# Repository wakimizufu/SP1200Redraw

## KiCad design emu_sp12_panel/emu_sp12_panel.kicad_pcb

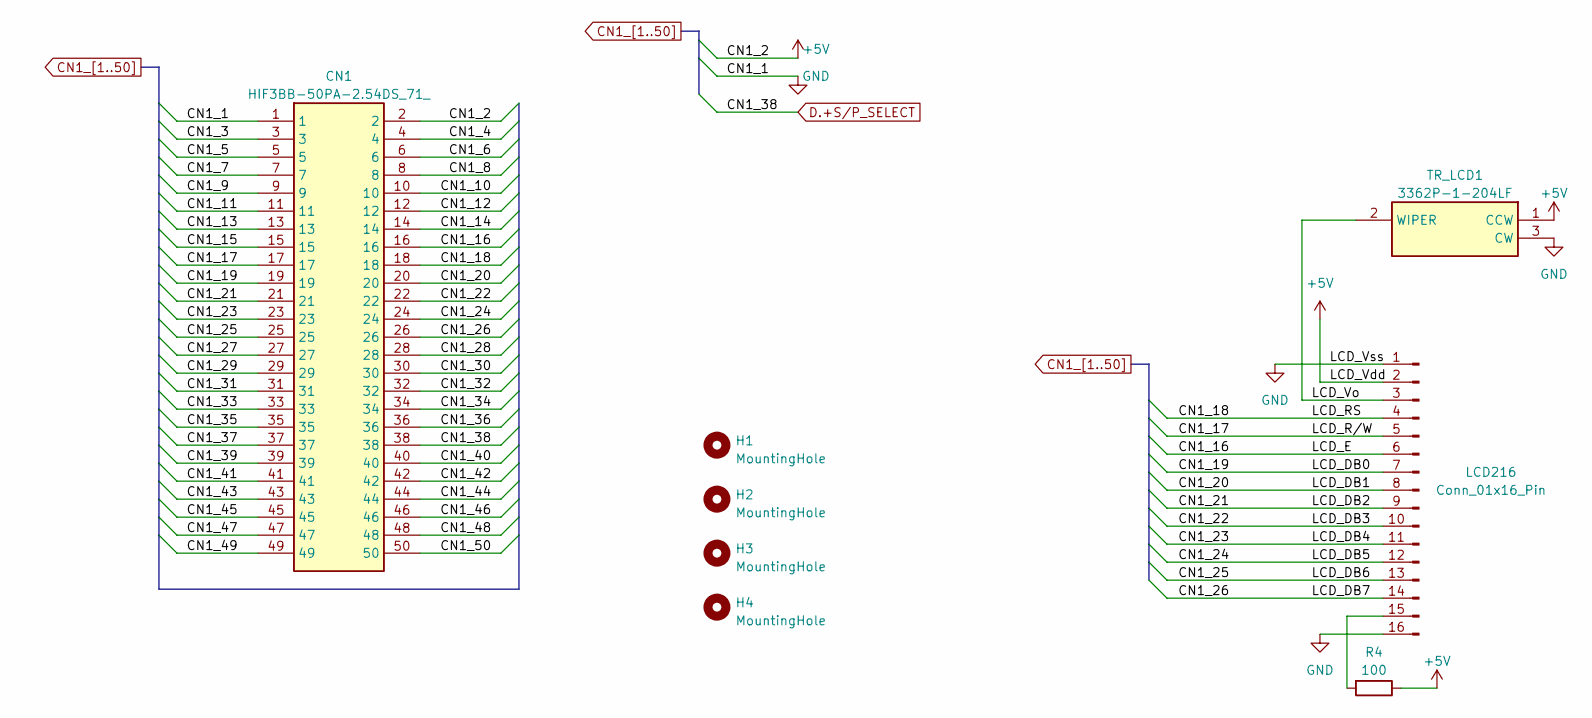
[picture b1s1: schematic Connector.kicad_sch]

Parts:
CN1: HIF3BB-50PA-2.54DS_71_; HIF3BB50PA254DS71; Manufacturer_Part_Number HIF3BB-50PA-2.54DS(71); Mouser Part Number 798-HIF3BB50PA254DS1
H1, H2, H3, H4: MountingHole; MountingHole_3.2mm_M3
LCD216: Conn_01x16_Pin; PinHeader_1x16_P2.54mm_Vertical
R4: 100; R_Axial_DIN0207_L6.3mm_D2.5mm_P5.08mm_Vertical
TR_LCD1: 3362P-1-204LF; 3362P_1; Manufacturer_Part_Number 3362P-1-103LF; Mouser Part Number 652-3362P-1-103LF

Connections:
/Connector/LCD_Vo: LCD216.3, TR_LCD1.2 (WIPER)
CN1_3: CN1.3; also elsewhere on the board
CN1_4: CN1.4; also elsewhere on the board
CN1_5: CN1.5; also elsewhere on the board
CN1_6: CN1.6; also elsewhere on the board
CN1_7: CN1.7; also elsewhere on the board
CN1_8: CN1.8; also elsewhere on the board
CN1_9: CN1.9; also elsewhere on the board
CN1_10: CN1.10
CN1_11: CN1.11; also elsewhere on the board
CN1_12: CN1.12; also elsewhere on the board
CN1_14: CN1.14; also elsewhere on the board
CN1_15: CN1.15; also elsewhere on the board
CN1_16: CN1.16, LCD216.6
CN1_17: CN1.17, LCD216.5
CN1_18: CN1.18, LCD216.4
CN1_19: CN1.19, LCD216.7
CN1_20: CN1.20, LCD216.8
CN1_21: CN1.21, LCD216.9
CN1_22: CN1.22, LCD216.10
CN1_23: CN1.23, LCD216.11
CN1_24: CN1.24, LCD216.12
CN1_25: CN1.25, LCD216.13
CN1_26: CN1.26, LCD216.14
CN1_27: CN1.27
CN1_28: CN1.28
CN1_29: CN1.29
CN1_30: CN1.30; also elsewhere on the board
CN1_31: CN1.31; also elsewhere on the board
CN1_32: CN1.32; also elsewhere on the board
CN1_33: CN1.33; also elsewhere on the board
CN1_34: CN1.34; also elsewhere on the board
CN1_35: CN1.35; also elsewhere on the board
CN1_36: CN1.36; also elsewhere on the board
CN1_37: CN1.37; also elsewhere on the board
CN1_39: CN1.39; also elsewhere on the board
CN1_40: CN1.40; also elsewhere on the board
CN1_41: CN1.41; also elsewhere on the board
CN1_42: CN1.42; also elsewhere on the board
CN1_43: CN1.43; also elsewhere on the board
CN1_44: CN1.44; also elsewhere on the board
CN1_45: CN1.45; also elsewhere on the board
CN1_46: CN1.46; also elsewhere on the board
CN1_47: CN1.47; also elsewhere on the board
CN1_48: CN1.48; also elsewhere on the board
CN1_49: CN1.49; also elsewhere on the board
CN1_50: CN1.50; also elsewhere on the board
D.+S/P_SELECT: CN1.38; also elsewhere on the board
GND: CN1.1, LCD216.1, LCD216.16, TR_LCD1.3 (CW); also elsewhere on the board

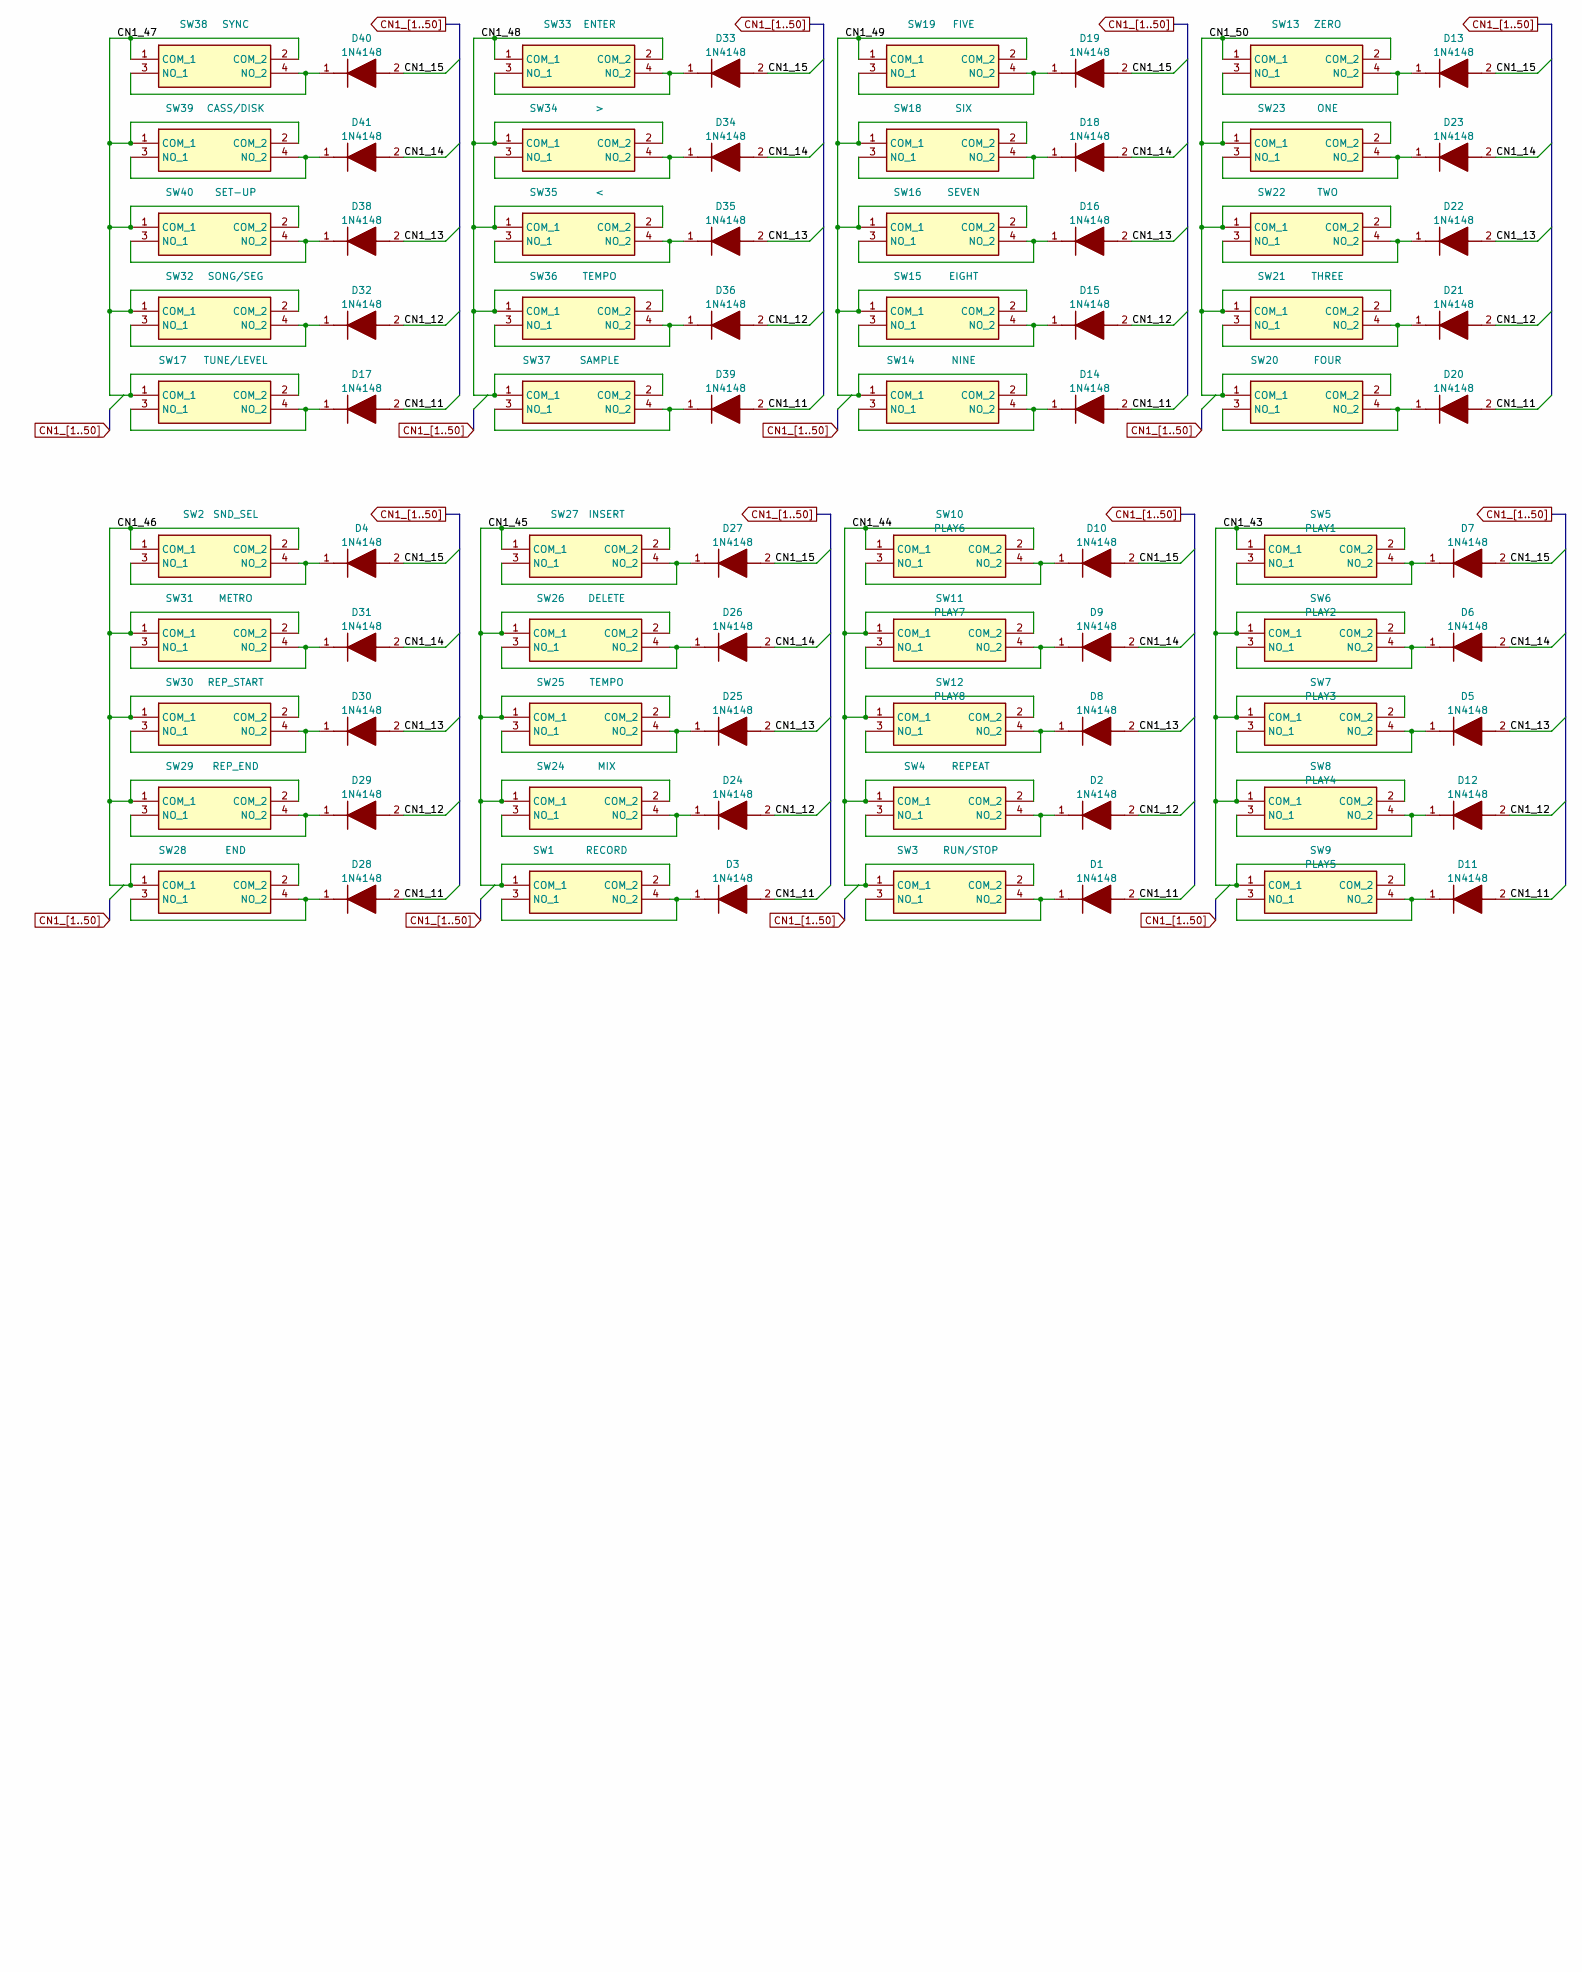
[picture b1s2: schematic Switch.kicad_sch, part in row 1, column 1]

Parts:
D1, D2, D3, D4, D5, D6, D7, D8, D9, D10, D11, D12, D13, D14, D15, D16, D17, D18, D19, D20, D21, D22, D23, D24, D25, D26, D27, D28, D29, D30, D31, D32, D33, D34, D35, D36, D38, D39, D40, D41: 1N4148; DIOAD1068W53L380D172; Manufacturer_Part_Number 1N4148; Mouser Part Number 512-1N4148
SW1: RECORD; DTS63NV; Manufacturer_Part_Number DTS-63N-V; Mouser Part Number 113-DTS-63N-V
SW2: SND_SEL; DTS63NV; Manufacturer_Part_Number DTS-63N-V; Mouser Part Number 113-DTS-63N-V
SW3: RUN/STOP; DTS63NV; Manufacturer_Part_Number DTS-63N-V; Mouser Part Number 113-DTS-63N-V
SW4: REPEAT; DTS63NV; Manufacturer_Part_Number DTS-63N-V; Mouser Part Number 113-DTS-63N-V
SW5: PLAY1; DTS63NV; Manufacturer_Part_Number TVGP01-G73BB
SW6: PLAY2; DTS63NV; Manufacturer_Part_Number TVGP01-G73BB
SW7: PLAY3; DTS63NV; Manufacturer_Part_Number TVGP01-G73BB
SW8: PLAY4; DTS63NV; Manufacturer_Part_Number TVGP01-G73BB
SW9: PLAY5; DTS63NV; Manufacturer_Part_Number TVGP01-G73BB
SW10: PLAY6; DTS63NV; Manufacturer_Part_Number TVGP01-G73BB
SW11: PLAY7; DTS63NV; Manufacturer_Part_Number TVGP01-G73BB
SW12: PLAY8; DTS63NV; Manufacturer_Part_Number TVGP01-G73BB
SW13: ZERO; DTS63NV; Manufacturer_Part_Number DTS-63N-V; Mouser Part Number 113-DTS-63N-V
SW14: NINE; DTS63NV; Manufacturer_Part_Number DTS-63N-V; Mouser Part Number 113-DTS-63N-V
SW15: EIGHT; DTS63NV; Manufacturer_Part_Number DTS-63N-V; Mouser Part Number 113-DTS-63N-V
SW16: SEVEN; DTS63NV; Manufacturer_Part_Number DTS-63N-V; Mouser Part Number 113-DTS-63N-V
SW17: TUNE/LEVEL; DTS63NV; Manufacturer_Part_Number DTS-63N-V; Mouser Part Number 113-DTS-63N-V
SW18: SIX; DTS63NV; Manufacturer_Part_Number DTS-63N-V; Mouser Part Number 113-DTS-63N-V
SW19: FIVE; DTS63NV; Manufacturer_Part_Number DTS-63N-V; Mouser Part Number 113-DTS-63N-V
SW20: FOUR; DTS63NV; Manufacturer_Part_Number DTS-63N-V; Mouser Part Number 113-DTS-63N-V
SW21: THREE; DTS63NV; Manufacturer_Part_Number DTS-63N-V; Mouser Part Number 113-DTS-63N-V
SW22: TWO; DTS63NV; Manufacturer_Part_Number DTS-63N-V; Mouser Part Number 113-DTS-63N-V
SW23: ONE; DTS63NV; Manufacturer_Part_Number DTS-63N-V; Mouser Part Number 113-DTS-63N-V
SW24: MIX; DTS63NV; Manufacturer_Part_Number DTS-63N-V; Mouser Part Number 113-DTS-63N-V
SW25, SW36: TEMPO; DTS63NV; Manufacturer_Part_Number DTS-63N-V; Mouser Part Number 113-DTS-63N-V
SW26: DELETE; DTS63NV; Manufacturer_Part_Number DTS-63N-V; Mouser Part Number 113-DTS-63N-V
SW27: INSERT; DTS63NV; Manufacturer_Part_Number DTS-63N-V; Mouser Part Number 113-DTS-63N-V
SW28: END; DTS63NV; Manufacturer_Part_Number DTS-63N-V; Mouser Part Number 113-DTS-63N-V
SW29: REP_END; DTS63NV; Manufacturer_Part_Number DTS-63N-V; Mouser Part Number 113-DTS-63N-V
SW30: REP_START; DTS63NV; Manufacturer_Part_Number DTS-63N-V; Mouser Part Number 113-DTS-63N-V
SW31: METRO; DTS63NV; Manufacturer_Part_Number DTS-63N-V; Mouser Part Number 113-DTS-63N-V
SW32: SONG/SEG; DTS63NV; Manufacturer_Part_Number DTS-63N-V; Mouser Part Number 113-DTS-63N-V
SW33: ENTER; DTS63NV; Manufacturer_Part_Number DTS-63N-V; Mouser Part Number 113-DTS-63N-V
SW34: >; DTS63NV; Manufacturer_Part_Number DTS-63N-V; Mouser Part Number 113-DTS-63N-V
SW35: <; DTS63NV; Manufacturer_Part_Number DTS-63N-V; Mouser Part Number 113-DTS-63N-V
SW37: SAMPLE; DTS63NV; Manufacturer_Part_Number DTS-63N-V; Mouser Part Number 113-DTS-63N-V
SW38: SYNC; DTS63NV; Manufacturer_Part_Number DTS-63N-V; Mouser Part Number 113-DTS-63N-V
SW39: CASS/DISK; DTS63NV; Manufacturer_Part_Number DTS-63N-V; Mouser Part Number 113-DTS-63N-V
SW40: SET-UP; DTS63NV; Manufacturer_Part_Number DTS-63N-V; Mouser Part Number 113-DTS-63N-V

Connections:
CN1_11: D1.2 (A), D3.2 (A), D11.2 (A), D14.2 (A), D17.2 (A), D20.2 (A), D28.2 (A), D39.2 (A); also elsewhere on the board
CN1_12: D2.2 (A), D12.2 (A), D15.2 (A), D21.2 (A), D24.2 (A), D29.2 (A), D32.2 (A), D36.2 (A); also elsewhere on the board
CN1_14: D6.2 (A), D9.2 (A), D18.2 (A), D23.2 (A), D26.2 (A), D31.2 (A), D34.2 (A), D41.2 (A); also elsewhere on the board
CN1_15: D4.2 (A), D7.2 (A), D10.2 (A), D13.2 (A), D19.2 (A), D27.2 (A), D33.2 (A), D40.2 (A); also elsewhere on the board
CN1_43: SW5.1 (COM_1), SW5.2 (COM_2), SW6.1 (COM_1), SW6.2 (COM_2), SW7.1 (COM_1), SW7.2 (COM_2), SW8.1 (COM_1), SW8.2 (COM_2), SW9.1 (COM_1), SW9.2 (COM_2); also elsewhere on the board
CN1_44: SW3.1 (COM_1), SW3.2 (COM_2), SW4.1 (COM_1), SW4.2 (COM_2), SW10.1 (COM_1), SW10.2 (COM_2), SW11.1 (COM_1), SW11.2 (COM_2), SW12.1 (COM_1), SW12.2 (COM_2); also elsewhere on the board
CN1_45: SW1.1 (COM_1), SW1.2 (COM_2), SW24.1 (COM_1), SW24.2 (COM_2), SW25.1 (COM_1), SW25.2 (COM_2), SW26.1 (COM_1), SW26.2 (COM_2), SW27.1 (COM_1), SW27.2 (COM_2); also elsewhere on the board
CN1_46: SW2.1 (COM_1), SW2.2 (COM_2), SW28.1 (COM_1), SW28.2 (COM_2), SW29.1 (COM_1), SW29.2 (COM_2), SW30.1 (COM_1), SW30.2 (COM_2), SW31.1 (COM_1), SW31.2 (COM_2); also elsewhere on the board
CN1_47: SW17.1 (COM_1), SW17.2 (COM_2), SW32.1 (COM_1), SW32.2 (COM_2), SW38.1 (COM_1), SW38.2 (COM_2), SW39.1 (COM_1), SW39.2 (COM_2), SW40.1 (COM_1), SW40.2 (COM_2); also elsewhere on the board
CN1_48: SW33.1 (COM_1), SW33.2 (COM_2), SW34.1 (COM_1), SW34.2 (COM_2), SW35.1 (COM_1), SW35.2 (COM_2), SW36.1 (COM_1), SW36.2 (COM_2), SW37.1 (COM_1), SW37.2 (COM_2); also elsewhere on the board
CN1_49: SW14.1 (COM_1), SW14.2 (COM_2), SW15.1 (COM_1), SW15.2 (COM_2), SW16.1 (COM_1), SW16.2 (COM_2), SW18.1 (COM_1), SW18.2 (COM_2), SW19.1 (COM_1), SW19.2 (COM_2); also elsewhere on the board
CN1_50: SW13.1 (COM_1), SW13.2 (COM_2), SW20.1 (COM_1), SW20.2 (COM_2), SW21.1 (COM_1), SW21.2 (COM_2), SW22.1 (COM_1), SW22.2 (COM_2), SW23.1 (COM_1), SW23.2 (COM_2); also elsewhere on the board
unnamed: D1.1 (K), SW3.3 (NO_1), SW3.4 (NO_2)
unnamed: D2.1 (K), SW4.3 (NO_1), SW4.4 (NO_2)
unnamed: D3.1 (K), SW1.3 (NO_1), SW1.4 (NO_2)
unnamed: D4.1 (K), SW2.3 (NO_1), SW2.4 (NO_2)
unnamed: D5.1 (K), SW7.3 (NO_1), SW7.4 (NO_2)
unnamed: D6.1 (K), SW6.3 (NO_1), SW6.4 (NO_2)
unnamed: D7.1 (K), SW5.3 (NO_1), SW5.4 (NO_2)
unnamed: D8.1 (K), SW12.3 (NO_1), SW12.4 (NO_2)
unnamed: D9.1 (K), SW11.3 (NO_1), SW11.4 (NO_2)
unnamed: D10.1 (K), SW10.3 (NO_1), SW10.4 (NO_2)
unnamed: D11.1 (K), SW9.3 (NO_1), SW9.4 (NO_2)
unnamed: D12.1 (K), SW8.3 (NO_1), SW8.4 (NO_2)
unnamed: D13.1 (K), SW13.3 (NO_1), SW13.4 (NO_2)
unnamed: D14.1 (K), SW14.3 (NO_1), SW14.4 (NO_2)
unnamed: D15.1 (K), SW15.3 (NO_1), SW15.4 (NO_2)
unnamed: D16.1 (K), SW16.3 (NO_1), SW16.4 (NO_2)
unnamed: D17.1 (K), SW17.3 (NO_1), SW17.4 (NO_2)
unnamed: D18.1 (K), SW18.3 (NO_1), SW18.4 (NO_2)
unnamed: D19.1 (K), SW19.3 (NO_1), SW19.4 (NO_2)
unnamed: D20.1 (K), SW20.3 (NO_1), SW20.4 (NO_2)
unnamed: D21.1 (K), SW21.3 (NO_1), SW21.4 (NO_2)
unnamed: D22.1 (K), SW22.3 (NO_1), SW22.4 (NO_2)
unnamed: D23.1 (K), SW23.3 (NO_1), SW23.4 (NO_2)
unnamed: D24.1 (K), SW24.3 (NO_1), SW24.4 (NO_2)
unnamed: D25.1 (K), SW25.3 (NO_1), SW25.4 (NO_2)
unnamed: D26.1 (K), SW26.3 (NO_1), SW26.4 (NO_2)
unnamed: D27.1 (K), SW27.3 (NO_1), SW27.4 (NO_2)
unnamed: D28.1 (K), SW28.3 (NO_1), SW28.4 (NO_2)
unnamed: D29.1 (K), SW29.3 (NO_1), SW29.4 (NO_2)
unnamed: D30.1 (K), SW30.3 (NO_1), SW30.4 (NO_2)
unnamed: D31.1 (K), SW31.3 (NO_1), SW31.4 (NO_2)
unnamed: D32.1 (K), SW32.3 (NO_1), SW32.4 (NO_2)
unnamed: D33.1 (K), SW33.3 (NO_1), SW33.4 (NO_2)
unnamed: D34.1 (K), SW34.3 (NO_1), SW34.4 (NO_2)
unnamed: D35.1 (K), SW35.3 (NO_1), SW35.4 (NO_2)
unnamed: D36.1 (K), SW36.3 (NO_1), SW36.4 (NO_2)
unnamed: D39.1 (K), SW37.3 (NO_1), SW37.4 (NO_2)
unnamed: D40.1 (K), SW38.3 (NO_1), SW38.4 (NO_2)
unnamed: D41.1 (K), SW39.3 (NO_1), SW39.4 (NO_2)

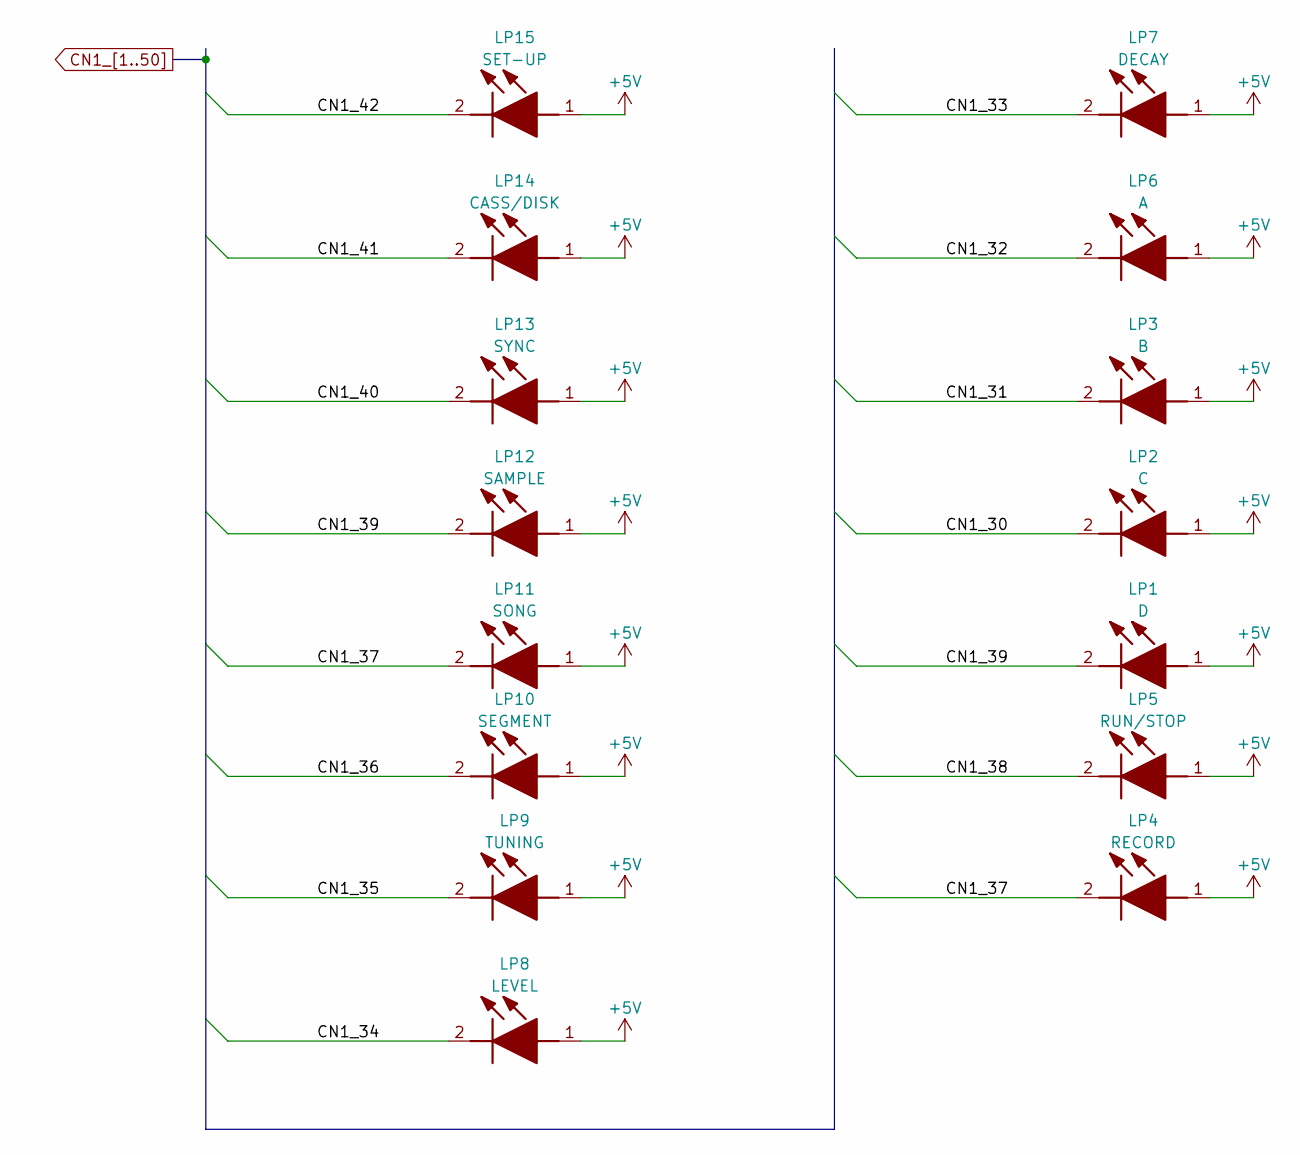
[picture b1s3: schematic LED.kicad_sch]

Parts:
LP1: D; LTL1CHKGKNN; Manufacturer_Part_Number LTL1CHKGKNN; Mouser Part Number 859-LTL1CHKGKNN
LP2: C; LTL1CHKGKNN; Manufacturer_Part_Number LTL1CHKGKNN; Mouser Part Number 859-LTL1CHKGKNN
LP3: B; LTL1CHKGKNN; Manufacturer_Part_Number LTL1CHKGKNN; Mouser Part Number 859-LTL1CHKGKNN
LP4: RECORD; LTL1CHKGKNN; Manufacturer_Part_Number LTL1CHKGKNN; Mouser Part Number 859-LTL1CHKGKNN
LP5: RUN/STOP; LTL1CHKGKNN; Manufacturer_Part_Number LTL1CHKGKNN; Mouser Part Number 859-LTL1CHKGKNN
LP6: A; LTL1CHKGKNN; Manufacturer_Part_Number LTL1CHKGKNN; Mouser Part Number 859-LTL1CHKGKNN
LP7: DECAY; LTL1CHKGKNN; Manufacturer_Part_Number LTL1CHKGKNN; Mouser Part Number 859-LTL1CHKGKNN
LP8: LEVEL; LTL1CHKGKNN; Manufacturer_Part_Number LTL1CHKGKNN; Mouser Part Number 859-LTL1CHKGKNN
LP9: TUNING; LTL1CHKGKNN; Manufacturer_Part_Number LTL1CHKGKNN; Mouser Part Number 859-LTL1CHKGKNN
LP10: SEGMENT; LTL1CHKGKNN; Manufacturer_Part_Number LTL1CHKGKNN; Mouser Part Number 859-LTL1CHKGKNN
LP11: SONG; LTL1CHKGKNN; Manufacturer_Part_Number LTL1CHKGKNN; Mouser Part Number 859-LTL1CHKGKNN
LP12: SAMPLE; LTL1CHKGKNN; Manufacturer_Part_Number LTL1CHKGKNN; Mouser Part Number 859-LTL1CHKGKNN
LP13: SYNC; LTL1CHKGKNN; Manufacturer_Part_Number LTL1CHKGKNN; Mouser Part Number 859-LTL1CHKGKNN
LP14: CASS/DISK; LTL1CHKGKNN; Manufacturer_Part_Number LTL1CHKGKNN; Mouser Part Number 859-LTL1CHKGKNN
LP15: SET-UP; LTL1CHKGKNN; Manufacturer_Part_Number LTL1CHKGKNN; Mouser Part Number 859-LTL1CHKGKNN

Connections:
CN1_30: LP2.2 (K); also elsewhere on the board
CN1_31: LP3.2 (K); also elsewhere on the board
CN1_32: LP6.2 (K); also elsewhere on the board
CN1_33: LP7.2 (K); also elsewhere on the board
CN1_34: LP8.2 (K); also elsewhere on the board
CN1_35: LP9.2 (K); also elsewhere on the board
CN1_36: LP10.2 (K); also elsewhere on the board
CN1_37: LP4.2 (K), LP11.2 (K); also elsewhere on the board
CN1_38: LP5.2 (K)
CN1_39: LP1.2 (K), LP12.2 (K); also elsewhere on the board
CN1_40: LP13.2 (K); also elsewhere on the board
CN1_41: LP14.2 (K); also elsewhere on the board
CN1_42: LP15.2 (K); also elsewhere on the board

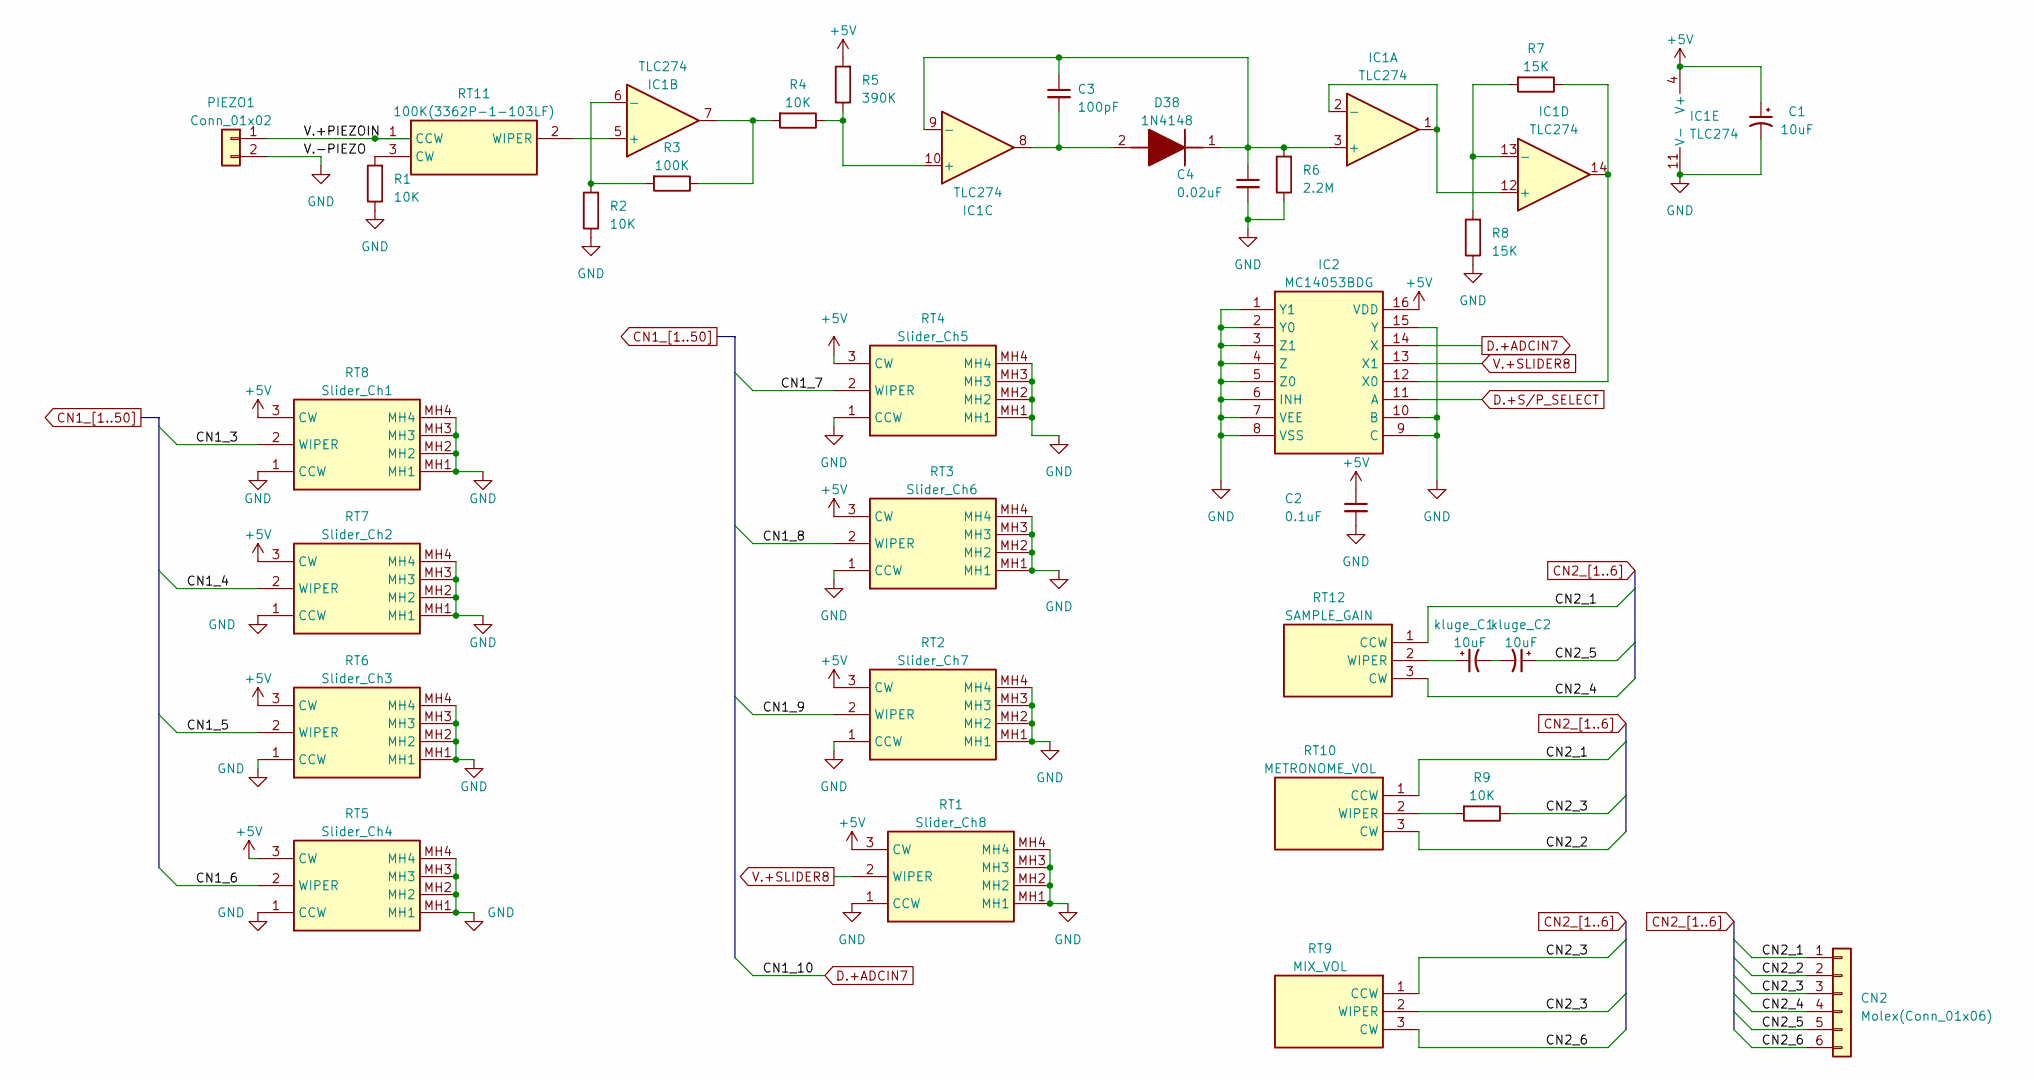
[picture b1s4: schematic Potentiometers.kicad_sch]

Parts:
C1: 10uF; CP_Radial_D5.0mm_P2.50mm
C2: 0.1uF; C_Rect_L7.0mm_W2.0mm_P5.00mm
C3: 100pF; C_Disc_D3.0mm_W2.0mm_P2.50mm
C4: 0.02uF; C_Rect_L7.0mm_W3.5mm_P5.00mm
CN2: Molex(Conn_01x06); PinHeader_1x06_P2.54mm_Vertical
D38: 1N4148; DIOAD1068W53L380D172; Manufacturer_Part_Number 1N4148; Mouser Part Number 512-1N4148
IC1: TLC274; DIP-14_W7.62mm_LongPads
IC2: MC14053BDG; DIP-16_W7.62mm_LongPads; Manufacturer_Part_Number MC14053BDG; Mouser Part Number 863-MC14053BDG
PIEZO1: Conn_01x02; PinHeader_1x02_P2.54mm_Vertical
R1, R2, R4, R9: 10K; R_Axial_DIN0207_L6.3mm_D2.5mm_P5.08mm_Vertical
R3: 100K; R_Axial_DIN0207_L6.3mm_D2.5mm_P5.08mm_Vertical
R5: 390K; R_Axial_DIN0207_L6.3mm_D2.5mm_P5.08mm_Vertical
R6: 2.2M; R_Axial_DIN0207_L6.3mm_D2.5mm_P5.08mm_Vertical
R7, R8: 15K; R_Axial_DIN0207_L6.3mm_D2.5mm_P5.08mm_Vertical
RT1: Slider_Ch8; PTA20432015DPB103; Manufacturer_Part_Number PTA2043-2015DPB103; Mouser Part Number 652-PTA2432015DPB103
RT2: Slider_Ch7; PTA20432015DPB103; Manufacturer_Part_Number PTA2043-2015DPB103; Mouser Part Number 652-PTA2432015DPB103
RT3: Slider_Ch6; PTA20432015DPB103; Manufacturer_Part_Number PTA2043-2015DPB103; Mouser Part Number 652-PTA2432015DPB103
RT4: Slider_Ch5; PTA20432015DPB103; Manufacturer_Part_Number PTA2043-2015DPB103; Mouser Part Number 652-PTA2432015DPB103
RT5: Slider_Ch4; PTA20432015DPB103; Manufacturer_Part_Number PTA2043-2015DPB103; Mouser Part Number 652-PTA2432015DPB103
RT6: Slider_Ch3; PTA20432015DPB103; Manufacturer_Part_Number PTA2043-2015DPB103; Mouser Part Number 652-PTA2432015DPB103
RT7: Slider_Ch2; PTA20432015DPB103; Manufacturer_Part_Number PTA2043-2015DPB103; Mouser Part Number 652-PTA2432015DPB103
RT8: Slider_Ch1; PTA20432015DPB103; Manufacturer_Part_Number PTA2043-2015DPB103; Mouser Part Number 652-PTA2432015DPB103
RT9: MIX_VOL; TSR3386TEY5103TR; Manufacturer_Part_Number TSR-3386T-EY5-103TR
RT10: METRONOME_VOL; TSR3386TEY5103TR; Manufacturer_Part_Number TSR-3386T-EY5-103TR
RT11: 100K(3362P-1-103LF); 3362P_1; Manufacturer_Part_Number 3362P-1-103LF; Mouser Part Number 652-3362P-1-103LF
RT12: SAMPLE_GAIN; TSR3386TEY5103TR; Manufacturer_Part_Number TSR-3386T-EY5-103TR
kluge_C1, kluge_C2: 10uF; CP_Radial_D5.0mm_P2.50mm

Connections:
/Potentiometers/V.+PIEZOIN: PIEZO1.1, RT11.1 (CCW)
CN1_3: RT8.2 (WIPER); also elsewhere on the board
CN1_4: RT7.2 (WIPER); also elsewhere on the board
CN1_5: RT6.2 (WIPER); also elsewhere on the board
CN1_6: RT5.2 (WIPER); also elsewhere on the board
CN1_7: RT4.2 (WIPER); also elsewhere on the board
CN1_8: RT3.2 (WIPER); also elsewhere on the board
CN1_9: RT2.2 (WIPER); also elsewhere on the board
CN2_1: CN2.1, RT10.1 (CCW), RT12.1 (CCW)
CN2_2: CN2.2, RT10.3 (CW)
CN2_3: CN2.3, R9.1, RT9.1 (CCW), RT9.2 (WIPER)
CN2_4: CN2.4, RT12.3 (CW)
CN2_5: CN2.5, kluge_C2.1
CN2_6: CN2.6, RT9.3 (CW)
D.+ADCIN7: IC2.14 (X)
D.+S/P_SELECT: IC2.11 (A); also elsewhere on the board
GND: C1.2, C2.2, C4.2, IC1.11 (V-), IC2.1 (Y1), IC2.2 (Y0), IC2.3 (Z1), IC2.4 (Z), IC2.5 (Z0), IC2.6 (INH), IC2.7 (VEE), IC2.8 (VSS), IC2.9 (C), IC2.10 (B), IC2.15 (Y), PIEZO1.2, R1.1, R2.1, R6.1, R8.1, RT1.1 (CCW), RT1.MH1, RT1.MH2, RT1.MH3, RT1.MH4, RT2.1 (CCW), RT2.MH1, RT2.MH2, RT2.MH3, RT2.MH4, RT3.1 (CCW), RT3.MH1, RT3.MH2, RT3.MH3, RT3.MH4, RT4.1 (CCW), RT4.MH1, RT4.MH2, RT4.MH3, RT4.MH4, RT5.1 (CCW), RT5.MH1, RT5.MH2, RT5.MH3, RT5.MH4, RT6.1 (CCW), RT6.MH1, RT6.MH2, RT6.MH3, RT6.MH4, RT7.1 (CCW), RT7.MH1, RT7.MH2, RT7.MH3, RT7.MH4, RT8.1 (CCW), RT8.MH1, RT8.MH2, RT8.MH3, RT8.MH4; also elsewhere on the board
unnamed: IC1.1, IC1.2 (-), IC1.12 (+)
unnamed: IC1.5 (+), RT11.2 (WIPER)
unnamed: IC1.6 (-), R2.2, R3.2
unnamed: IC1.13 (-), R7.2, R8.2
unnamed: IC1.14, IC2.12 (X0), R7.1
unnamed: R9.2, RT10.2 (WIPER)
unnamed: R1.2, RT11.3 (CW)
unnamed: RT12.2 (WIPER), kluge_C1.1
unnamed: kluge_C1.2, kluge_C2.2
V.+SLIDER8: IC2.13 (X1), RT1.2 (WIPER)

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
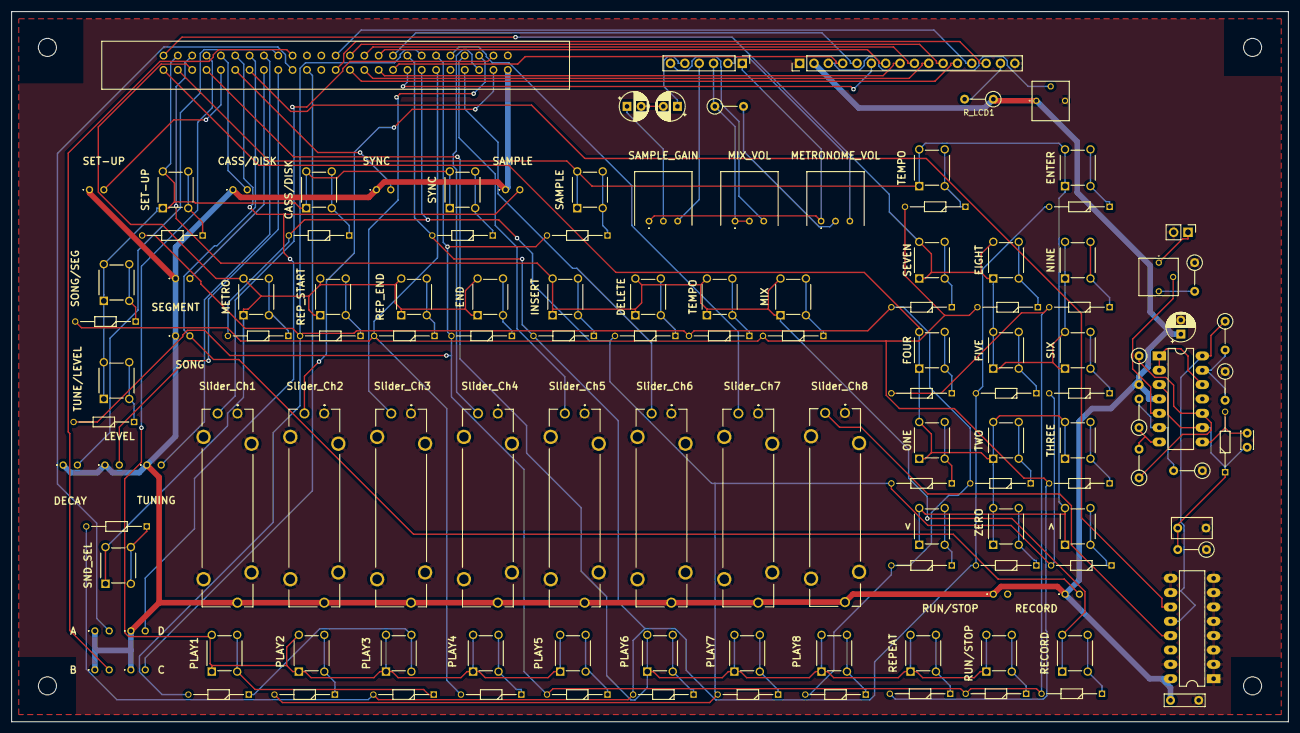
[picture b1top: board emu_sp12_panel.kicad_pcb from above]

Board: 2 copper layers, 226.1 x 125.7 mm, 135 parts (0 on the bottom side), 109 nets.

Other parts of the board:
D37: 1N4148; DIOAD1068W53L380D172
R_LCD1: 100; R_Axial_DIN0207_L6.3mm_D2.5mm_P5.08mm_Vertical

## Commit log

2024-05-16 addFiles
2024-05-16 firmware
